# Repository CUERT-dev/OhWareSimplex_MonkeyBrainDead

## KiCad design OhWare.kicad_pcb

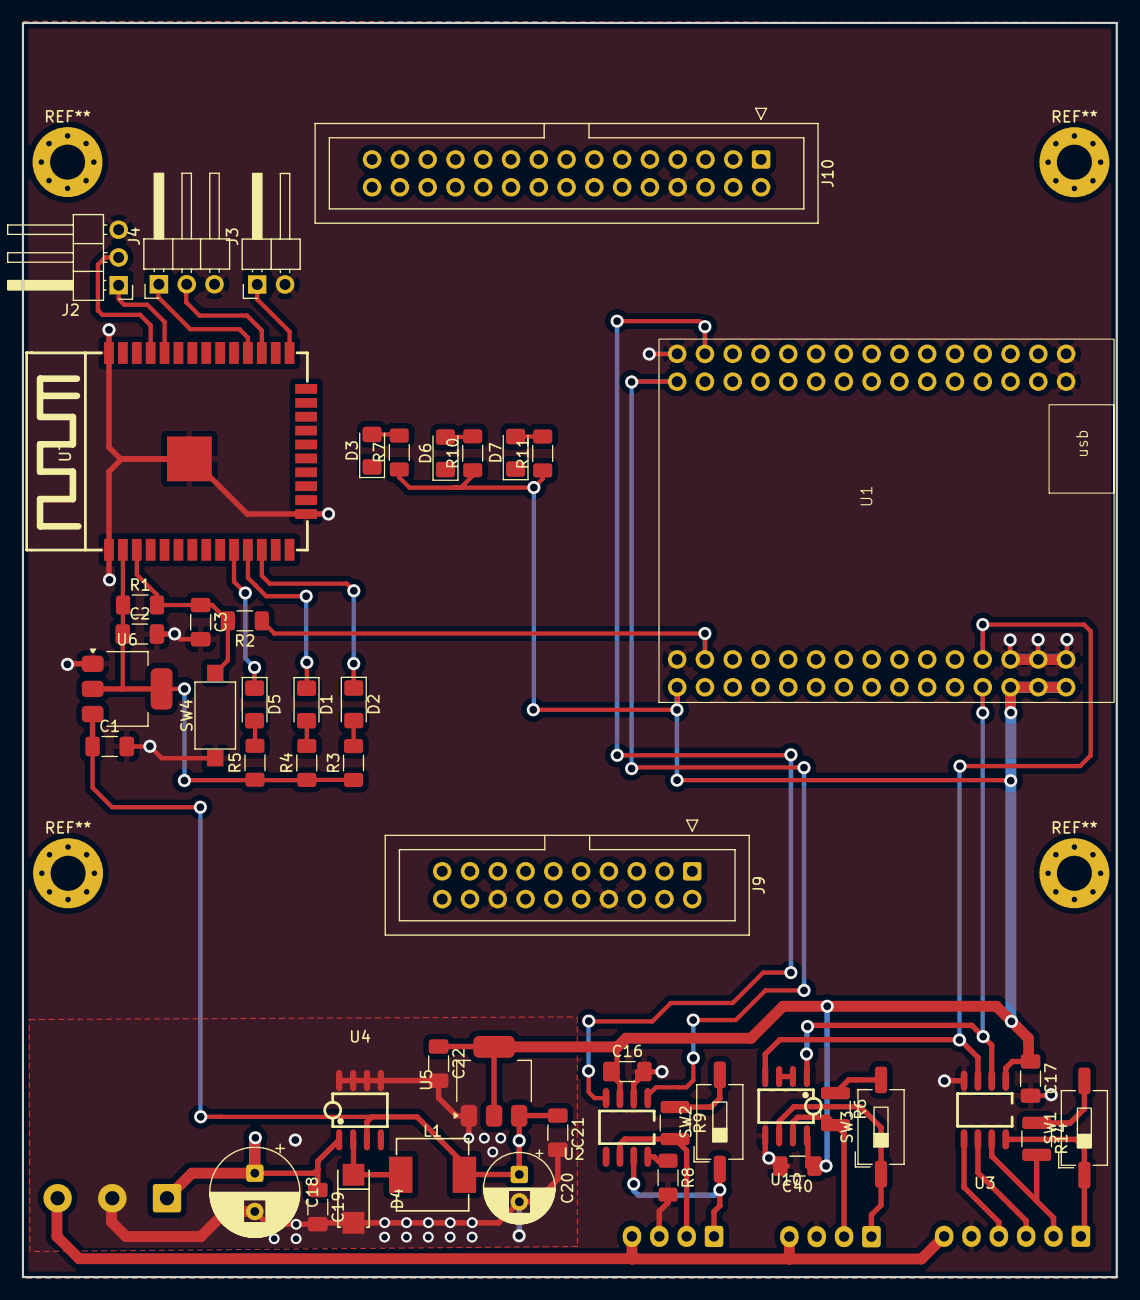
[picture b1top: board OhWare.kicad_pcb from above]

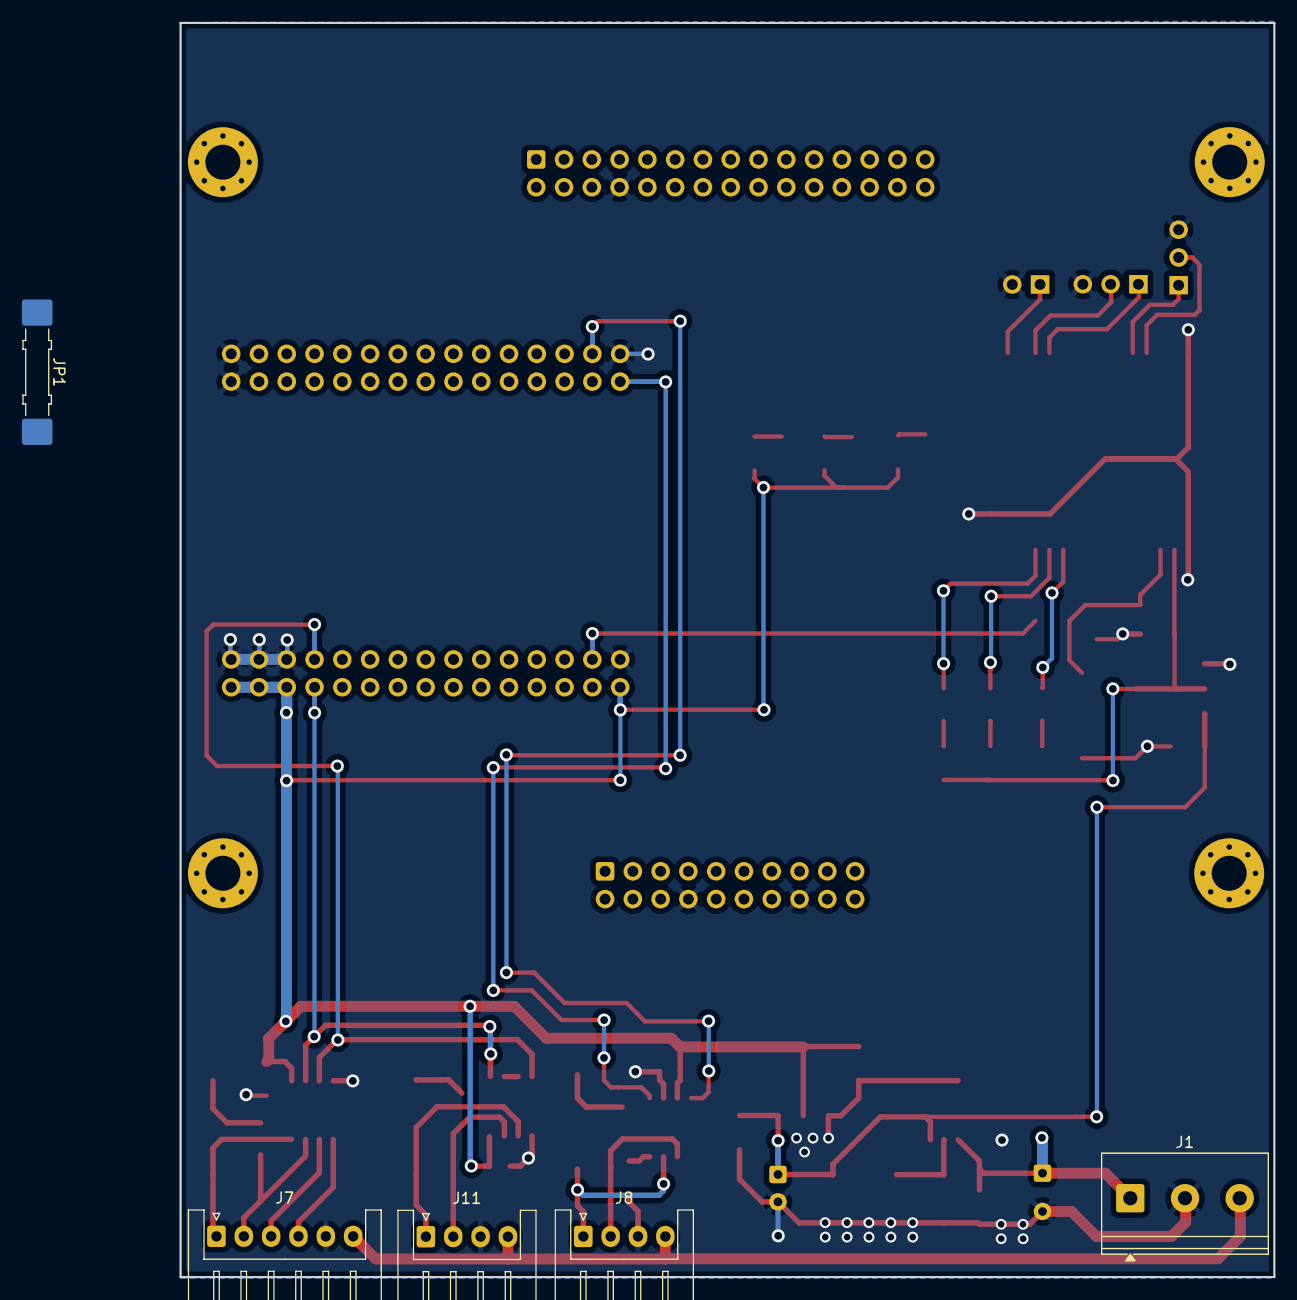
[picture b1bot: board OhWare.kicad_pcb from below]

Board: 2 copper layers, 100.0 x 114.7 mm, 53 parts (5 on the bottom side), 41 nets.

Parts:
C1, C2, C21, C22: 10u; C_1206_3216Metric_Pad1.33x1.80mm_HandSolder
C3, C17, C40: 0.1u; C_1206_3216Metric_Pad1.33x1.80mm_HandSolder
C16: 100n; C_1206_3216Metric_Pad1.33x1.80mm_HandSolder
C18: 100uF-35V; CP_Radial_D8.0mm_P3.50mm
C19: 1u-50V; C_1206_3216Metric_Pad1.33x1.80mm_HandSolder
C20: 180uF-10V; CP_Radial_D6.3mm_P2.50mm
D1, D2, D3, D5, D6, D7: LED; LED_1206_3216Metric_Pad1.42x1.75mm_HandSolder
D4: SS34_C8678; SMA_L4.3-W2.6-LS5.2-RD
J1: Screw_Terminal_01x03; TerminalBlock_Phoenix_PT-1,5-3-5.0-H_1x03_P5.00mm_Horizontal
J2, J4: Conn_01x03_Pin; PinHeader_1x03_P2.54mm_Horizontal
J3: Conn_01x02_Pin; PinHeader_1x02_P2.54mm_Horizontal
J7: Conn_01x06_Pin; JST_XH_S6B-XH-A_1x06_P2.50mm_Horizontal
J8, J11: Conn_01x04_Pin; JST_XH_S4B-XH-A_1x04_P2.50mm_Horizontal
J9: Conn_02x10_Odd_Even; IDC-Header_2x10_P2.54mm_Vertical
J10: Conn_02x15_Odd_Even; IDC-Header_2x15_P2.54mm_Vertical
JP1: Jumper_2_Bridged; Jumper_Harwin_S1621_P10.9mm
L1: SMMS0650-680M; IND-SMD_L7.1-W6.6_H5.0
R1, R8: 10k; R_1206_3216Metric_Pad1.30x1.75mm_HandSolder
R2: 470; R_1206_3216Metric_Pad1.30x1.75mm_HandSolder
R3, R4, R5, R7, R10, R11: 1k; R_1206_3216Metric_Pad1.30x1.75mm_HandSolder
R6, R9, R14: 120; R_1210_3225Metric
SW1, SW2, SW3: SW_DIP_x01; SW_DIP_SPSTx01_Slide_6.7x4.1mm_W8.61mm_P2.54mm_LowProfile
SW4: SW_Push; SW_SPST_CK_RS282G05A3
U1: WeAct_STM32F12
U2: SIT65HVD230DR; SOP-8_L4.9-W3.9-P1.27-LS6.0-BL
U3: SIT3490EESA; SOP-8_L4.9-W3.9-P1.27-LS6.0-BL
U4: XL1509-5.0E1; SOIC-8_L5.0-W4.0-P1.27-LS6.0-BL
U5, U6: AMS1117-3.3; SOT-223-3_TabPin2
U7: ESP32-WROOM-32; WIFIM-SMD_ESP32-WROOM-32-N4
U10: SP3485EN-L/TR; SOIC-8_L5.0-W4.0-P1.27-LS6.0-BL

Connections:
+3.3V: C16.1, C17.1, C22.1, C40.1, R7.1, R10.1, R11.1, U1.1 (VB), U1.25 (3.3), U1.27 (3.3), U1.29 (3.3), U2.3 (VCC), U3.1 (VCC), U5.2 (VO), U10.8 (VCC)
+3.3VESP: C2.1, R1.1, R3.1, R4.1, R5.1, U6.2 (VO), U7.2 (3V3)
+5V: C1.1, C20.1, C21.1, L1.2, U4.3 (FB), U5.3 (VI), U6.3 (VI)
+12V: C18.1, C19.1, J1.1, U4.1 (VIN)
/CAN/CAN_H: J8.1, SW2.1, U2.7 (CANH)
/CAN/CAN_L: J8.2, R9.2, U2.6 (CANL)
/CAN/CAN_RXD: U1.34 (B8), U2.4 (R)
/CAN/CAN_TXD: U1.31 (B9), U2.1 (D)
/Controller/SPI3_DEN: R2.1, U1.4 (C13)
/Controller/USART3_RX: U1.23 (B11), U3.2 (RO), U10.1 (RO)
/Controller/USART3_TX: U1.24 (B10), U3.3 (DI), U10.4 (DI)
/Esp32/INDESP_LED0: D5.1 (K), U7.10 (IO25)
/Esp32/INDESP_LED1: D1.1 (K), U7.11 (IO26)
/Esp32/INDESP_LED2: D2.1 (K), U7.12 (IO27)
/Esp32/SPI_MISO: JP1.2 (B), U7.14 (IO12)
/RS485/A: J7.1, SW1.1, U3.8 (A)
/RS485/A2: J11.1, SW3.1, U10.6 (A)
/RS485/B: J7.2, R14.2, U3.7 (B)
/RS485/B2: J11.2, R6.2, U10.7 (B)
/RS485/Y: J7.4, U3.5 (Y)
/RS485/Z: J7.3, U3.6 (Z)
/RS485/nRE/DE: U10.2 (~RE), U10.3 (DE)
Earth: J1.3, J7.6, J8.4, J11.4
GND: C1.2, C2.2, C3.2, C16.2, C17.2, C18.2, C19.2, C20.2, C21.2, C22.2, C40.2, D4.2 (A), J1.2, J2.3, J3.2, J4.3, J7.5, J8.3, J9.8, J9.16, J10.8, J11.3, R8.2, SW4.1, U1.2 (GND), U1.26 (GND), U1.28 (GND), U1.30 (GND), U1.32 (GND), U1.59 (GND), U1.60 (GND), U2.2 (GND), U3.4 (GND), U4.5 (GND), U4.6 (GND), U4.7 (GND), U4.8 (GND), U5.1 (GND), U6.1 (GND), U7.1 (GND), U7.15 (GND), U7.38 (GND), U7.39 (GND), U10.5 (GND)
unnamed: D1.2 (A), R4.2
unnamed: D2.2 (A), R3.2
unnamed: D3.2 (A), R7.2
unnamed: D4.1 (K), L1.1, U4.2 (OUTPUT)
unnamed: D5.2 (A), R5.2
unnamed: D6.2 (A), R10.2
unnamed: D7.2 (A), R11.2
unnamed: J2.1, U7.34 (RXD0)
unnamed: J2.2, U7.35 (TXD0)
unnamed: J3.1, U7.25 (IO0)
unnamed: J4.1, U7.28 (IO17)
unnamed: J4.2, U7.27 (IO16)
unnamed: R6.1, SW3.2
unnamed: R9.1, SW2.2
unnamed: R14.1, SW1.2
unnamed: R8.1, U2.8 (RS)
unnamed: C3.1, R1.2, R2.2, SW4.2, U7.3 (EN)

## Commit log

2025-11-05 Key CHanges for connector choices , termination and semi-final decisions on them
2025-11-14 Done routing for Buck Converter , Rs485 and CAN , Some Routing for MCU and associated circuitry , NO ETHERNET ROUTING , NO module Interconnects yet
2025-11-14 mcu circuit Done , + Ehernet Done (still placement is negotiable (best placement for minimal routing hustle))
2025-11-19 Added Base
2025-11-20 Latest Changes
